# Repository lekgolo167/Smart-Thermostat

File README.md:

# Enxor-Smart-Thermostat
## Hardware
### By: Matthew Crump
---
## Contents
1. [Overview](#overview)
2. [General Design](#general-design)
3. [Built-in Self Test](#built-in-self-test)
4. [Wiring Diagram](#wiring-diagram)
5. [PCB Design](#pcb-design)
---
## Overview
At my duplex, I used to have a simple thermostat that used a mercury switch. I wanted to improve this by making a smart thermostat that could have a different schedule for each day of the week. As a college student at the time of creation, my schedule varied day by day. Another feature I wanted was to have the termostat automatically turn down after I had been away for a certain amount of time. The sensor data is sent to a influx database running on a Raspberry Pi. The schedule has a hard-coded default on startup but loads the server-side schedule once connected to the network. The thermostat can also show a 3-day weather forecast.
[Thermostat UI and Server Repository](https://github.com/lekgolo167/Thermostat-UI)

---
## General Design
The main event loop checks if a global queue has any items in it. Each item in the queue is a message with a corrisponding case statement block. This made it easy to connect all the classes/components together, like the OLED menu being able to change settings for the back-end. The user interface is interrupt driven, and each interrupt function adds a message to the global queue.
Timers are used to trigger sensor reading events. Which can be in intervals of 5 seconds and up to 3 minutes in-between. At each sensor reading event, the thermostat determines if the furnace should turn on based on the day's schedule or if the temperature is below the baseline. A baseline temperature is maintained if no motion has been detected for X amount of hours which is settable by the user.

## Built-in Self Test
Both the HDC1080 and HTU21D temperature sensors feature a built-in heater that can be used to test the sensor. I used a Z score value of 5 or greater to determine whether the sensor is working or not. Using a standard deviation of the sensor readings might not be the best way to know if the sesnor is working but it made it easier to do a peak detection of the sensor readings rather than just hardcoding a check that just waits for the sensor reading to go one degree from where it started.
The self test is ran once a month and helps clear off any condensation build up on the sensor package. The results of the self test (pass or fail) are logged to the server.

---
## Wiring Diagram

---
## PCB Design
Front

Back

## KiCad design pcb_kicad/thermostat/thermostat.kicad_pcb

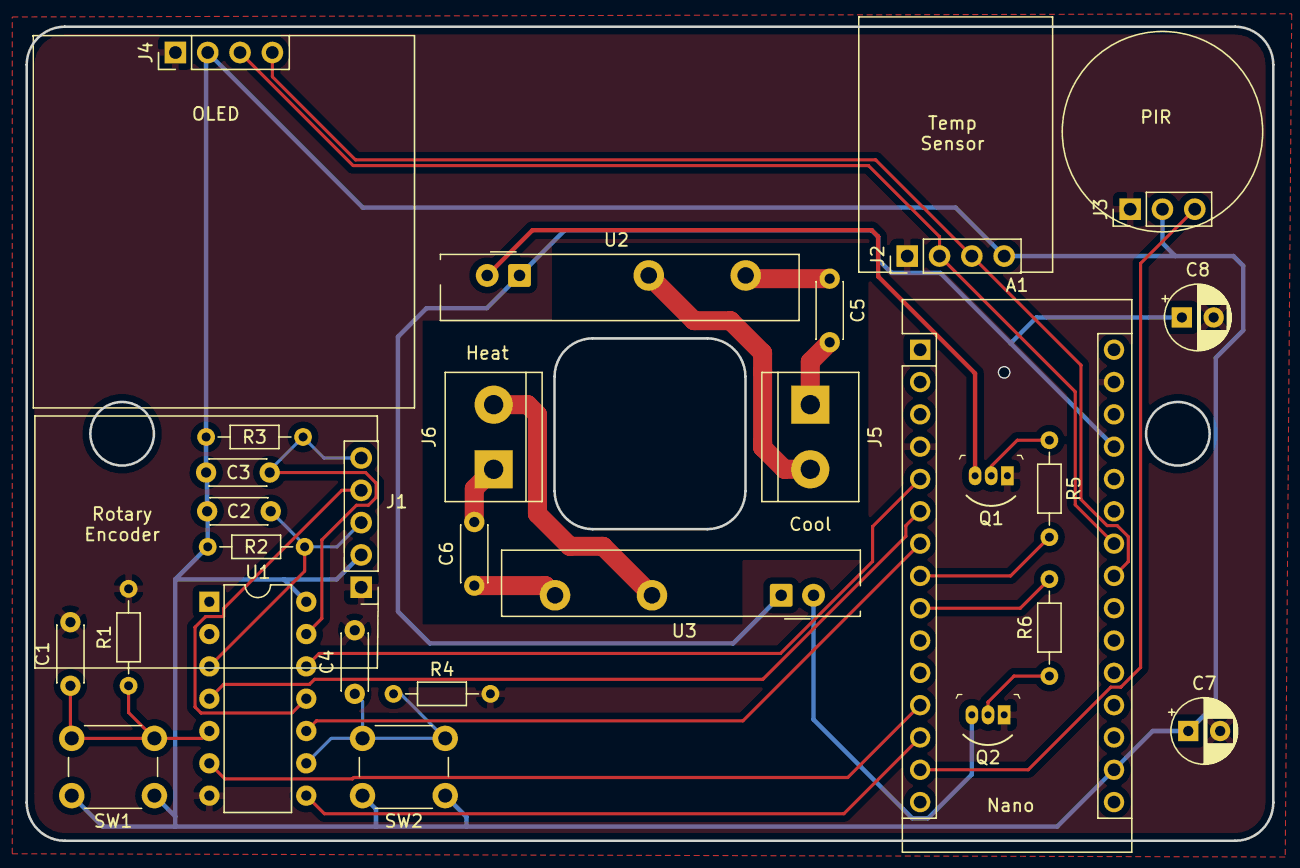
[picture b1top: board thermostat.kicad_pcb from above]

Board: 2 copper layers, 98.0 x 64.0 mm, 28 parts (0 on the bottom side), 28 nets.

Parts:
A1: Arduino_Nano_v3.x; Arduino_Nano
C1, C2, C3, C4, C5, C6: C; C_Disc_D4.3mm_W1.9mm_P5.00mm
C7, C8: CP; CP_Radial_D5.0mm_P2.50mm
J1: Rotary Encoder; PinHeader_1x05_P2.54mm_Vertical
J2: HDC1080; PinHeader_1x04_P2.54mm_Vertical
J3: IR Motion; PinHeader_1x03_P2.54mm_Vertical
J4: OLED; PinHeader_1x04_P2.54mm_Vertical
J5, J6: Conn_01x02_Female; TerminalBlock_bornier-2_P5.08mm
Q1, Q2: PN2222A; TO-92-3
R1, R2, R3, R4, R5, R6: R; R_Axial_DIN0204_L3.6mm_D1.6mm_P7.62mm_Horizontal
SW1, SW2: SW_DPST; SW_PUSH_6mm
U1: 74HC14; DIP-14_W7.62mm
U2, U3: G3MB-202p; OMEON_G3MB-202P

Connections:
3.3v: A1.17, C2.2, C3.1, C7.1, J1.2, J2.4, J3.2, J4.2, R2.1, R3.2, SW1.1, SW2.1, U1.14
5.0v: A1.27, C8.1, U2.A1, U3.A1
AC: A1.8, R5.2
BTN_A: A1.12, U1.6
BTN_B: A1.13, U1.8
GND: A1.4, A1.29, C1.2, C4.2, C7.2, C8.2, J1.1, J2.1, J3.1, J4.1, Q1.1, Q2.1, R1.2, R4.2, U1.7
Heat: A1.9, R6.2
IR: A1.14, J3.3
unnamed: C1.1, R1.1, SW1.2, U1.5
unnamed: C2.1, J1.3, R2.2, U1.3
unnamed: C3.2, J1.5, R3.1, U1.13
unnamed: C4.1, R4.1, SW2.2, U1.9
unnamed: C5.1, U2.14
unnamed: C5.2, J5.1
unnamed: C6.1, U3.14
unnamed: C6.2, J6.1
unnamed: J1.4, U1.11
unnamed: J5.2, U2.11
unnamed: J6.2, U3.11
unnamed: Q1.2, R5.1
unnamed: Q1.3, U2.A2
unnamed: Q2.2, R6.1
unnamed: Q2.3, U3.A2
ROT_A: A1.5, U1.12
ROT_B: A1.7, U1.10
ROT_SW: A1.6, U1.4
SCL: A1.24, J2.2, J4.3
SDA: A1.23, J2.3, J4.4

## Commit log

2021-07-12 oled menu code
2021-07-12 Added SAMD datasheet
2021-07-12 ISR functions connected
2021-07-17 OLED
2021-07-18 more oled
2021-08-09 Added message queue to improve flow control and interrupts
2021-08-09 Added message queue
2021-08-10 Added motion timer using TC3
2021-08-11 Motion timeout works
2021-08-12 wifi
2021-08-13 fixed unit tests for native build
2021-08-19 Added temporary override and server communication
2021-08-20 Can fetch and update cycles from server
2021-08-21 Added POST requests, RTC Sync, and screen on for user-input
2021-08-21 Fixed cycle end time for OLED menu
2021-10-28 check if server is active before http request
2021-11-01 dynamic history graph
2022-03-11 oled menu update
2022-03-11 Weather data/forecast displays
2022-03-12 Weather data and hourly weather
2022-03-12 Inverting IO logic for use with inverting Shmitt triggers
2022-03-14 fixed weather data struct copy and reject bad temperature readings
2022-03-16 WiFI menu and IP address is now discovered through hostname
2022-06-14 PCB Rev 1.0
2022-06-15 readme added
2022-07-01 Kalman and Averaging filters and self test logic
2022-07-04 Added logging to server
2022-07-04 Fix logging port
2022-10-14 No wonder the furnace doesn't turn on. I was using the wrong pin :(
2022-10-14 Use WiFi low power mode and RTC
2023-05-06 udate weather icons to match new forecast api
2023-09-22 sleep mode
